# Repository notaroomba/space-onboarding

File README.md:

# MIT Rocket/Satellite Team Onboarding Files
`/avionics` for rocket avionics stuff
`/satellite ` for satellite stuff
`/propulsion` for prop cad stuff

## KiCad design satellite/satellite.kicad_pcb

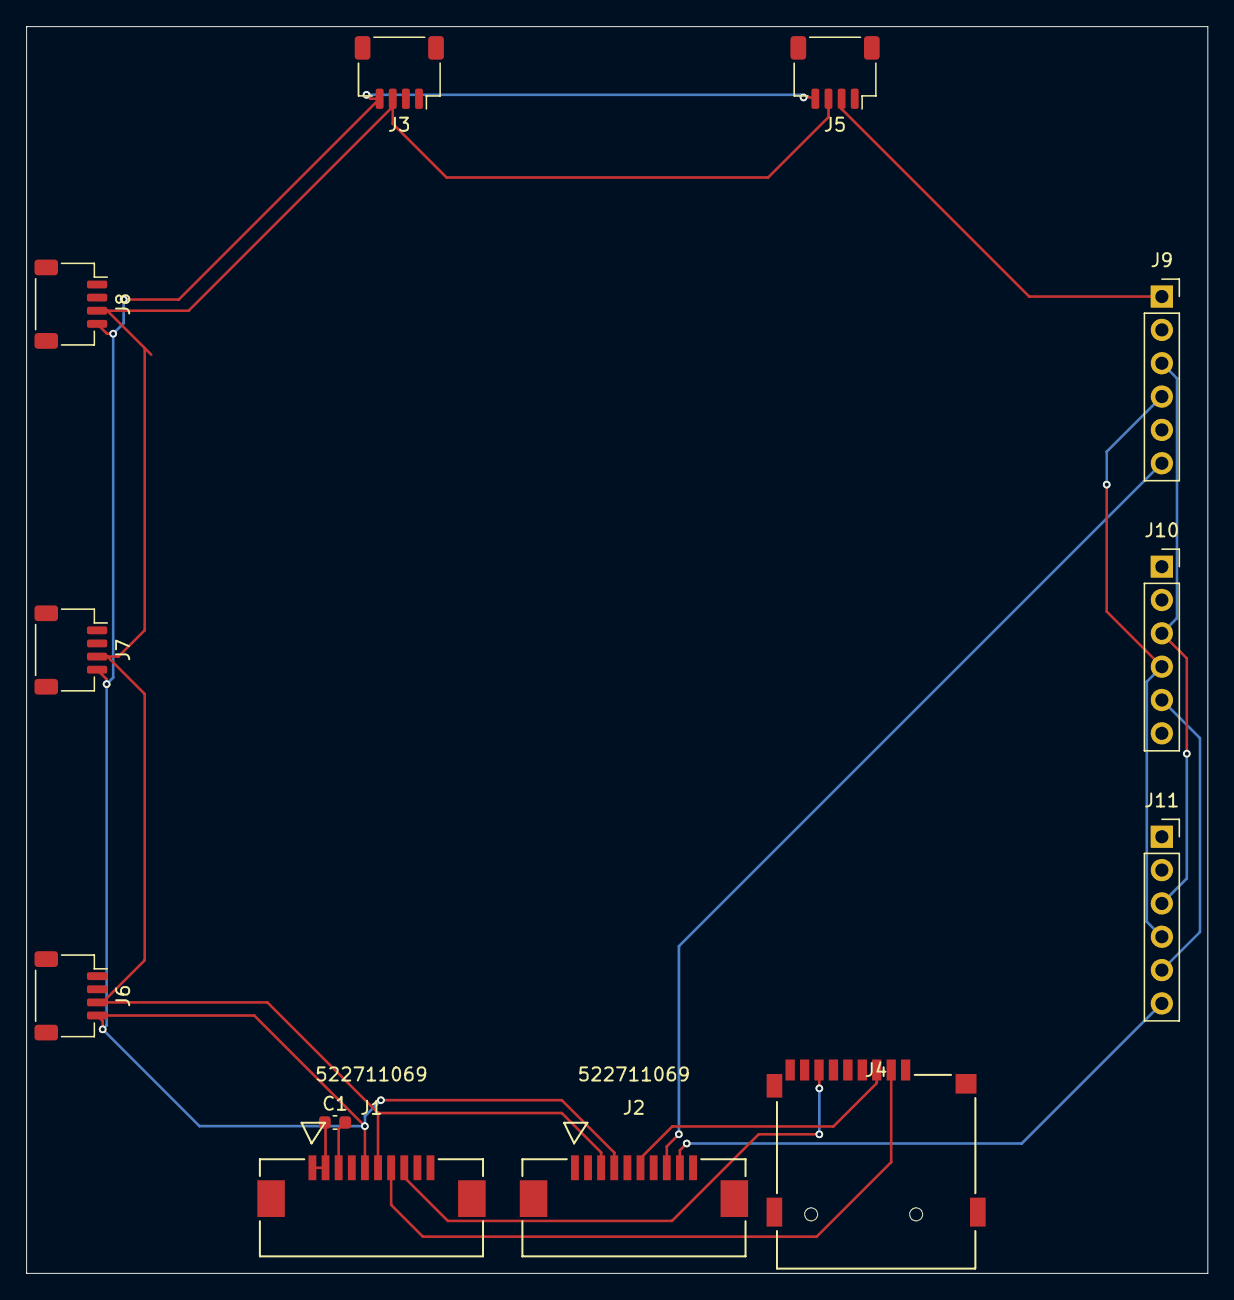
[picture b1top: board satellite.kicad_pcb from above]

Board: 2 copper layers, 90.0 x 95.0 mm, 12 parts (0 on the bottom side), 11 nets.

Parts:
C1: 100nF; C_0603_1608Metric
J1, J2: CON_522711069_MOL
J3, J5, J6, J7, J8: Conn_01x04_Pin; JST_SH_SM04B-SRSS-TB_1x04-1MP_P1.00mm_Horizontal
J4: Micro_SD_Card; CONN9_MSD-4-A_SSD
J9, J10, J11: Conn_01x06_Pin; PinSocket_1x06_P2.54mm_Vertical

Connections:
+3V3: C1.1, J1.1, J1.2, J3.2, J4.4 (VDD), J5.2, J6.2, J7.2, J8.2, J9.1, J10.1, J11.1
/GPIO3: J1.7, J4.2 (DAT3/CD)
/GPIO8: J2.8, J9.6
/GPIO9: J2.9, J11.6
/GPIO18: J2.2, J10.6
/SCL: J1.5, J2.4, J3.4, J5.4, J6.4, J7.4, J8.4
/SDA: J1.6, J2.3, J3.3, J5.3, J6.3, J7.3, J8.3
/SPI0_CLK: J1.10, J4.5 (CLK), J9.3, J10.3, J11.3
/SPI0_RX: J1.8, J4.7 (DAT0), J9.4, J10.4, J11.4
/SPI0_TX: J2.6, J4.3 (CMD), J9.5, J10.5, J11.5
GND: C1.2, J1.3, J1.4, J1.P1 (MountPin), J1.P2 (MountPin), J2.1, J2.5, J2.7, J2.10, J2.P1 (MountPin), J2.P2 (MountPin), J3.1, J4.6 (VSS), J5.1, J6.1, J7.1, J8.1, J9.2, J10.2, J11.2
